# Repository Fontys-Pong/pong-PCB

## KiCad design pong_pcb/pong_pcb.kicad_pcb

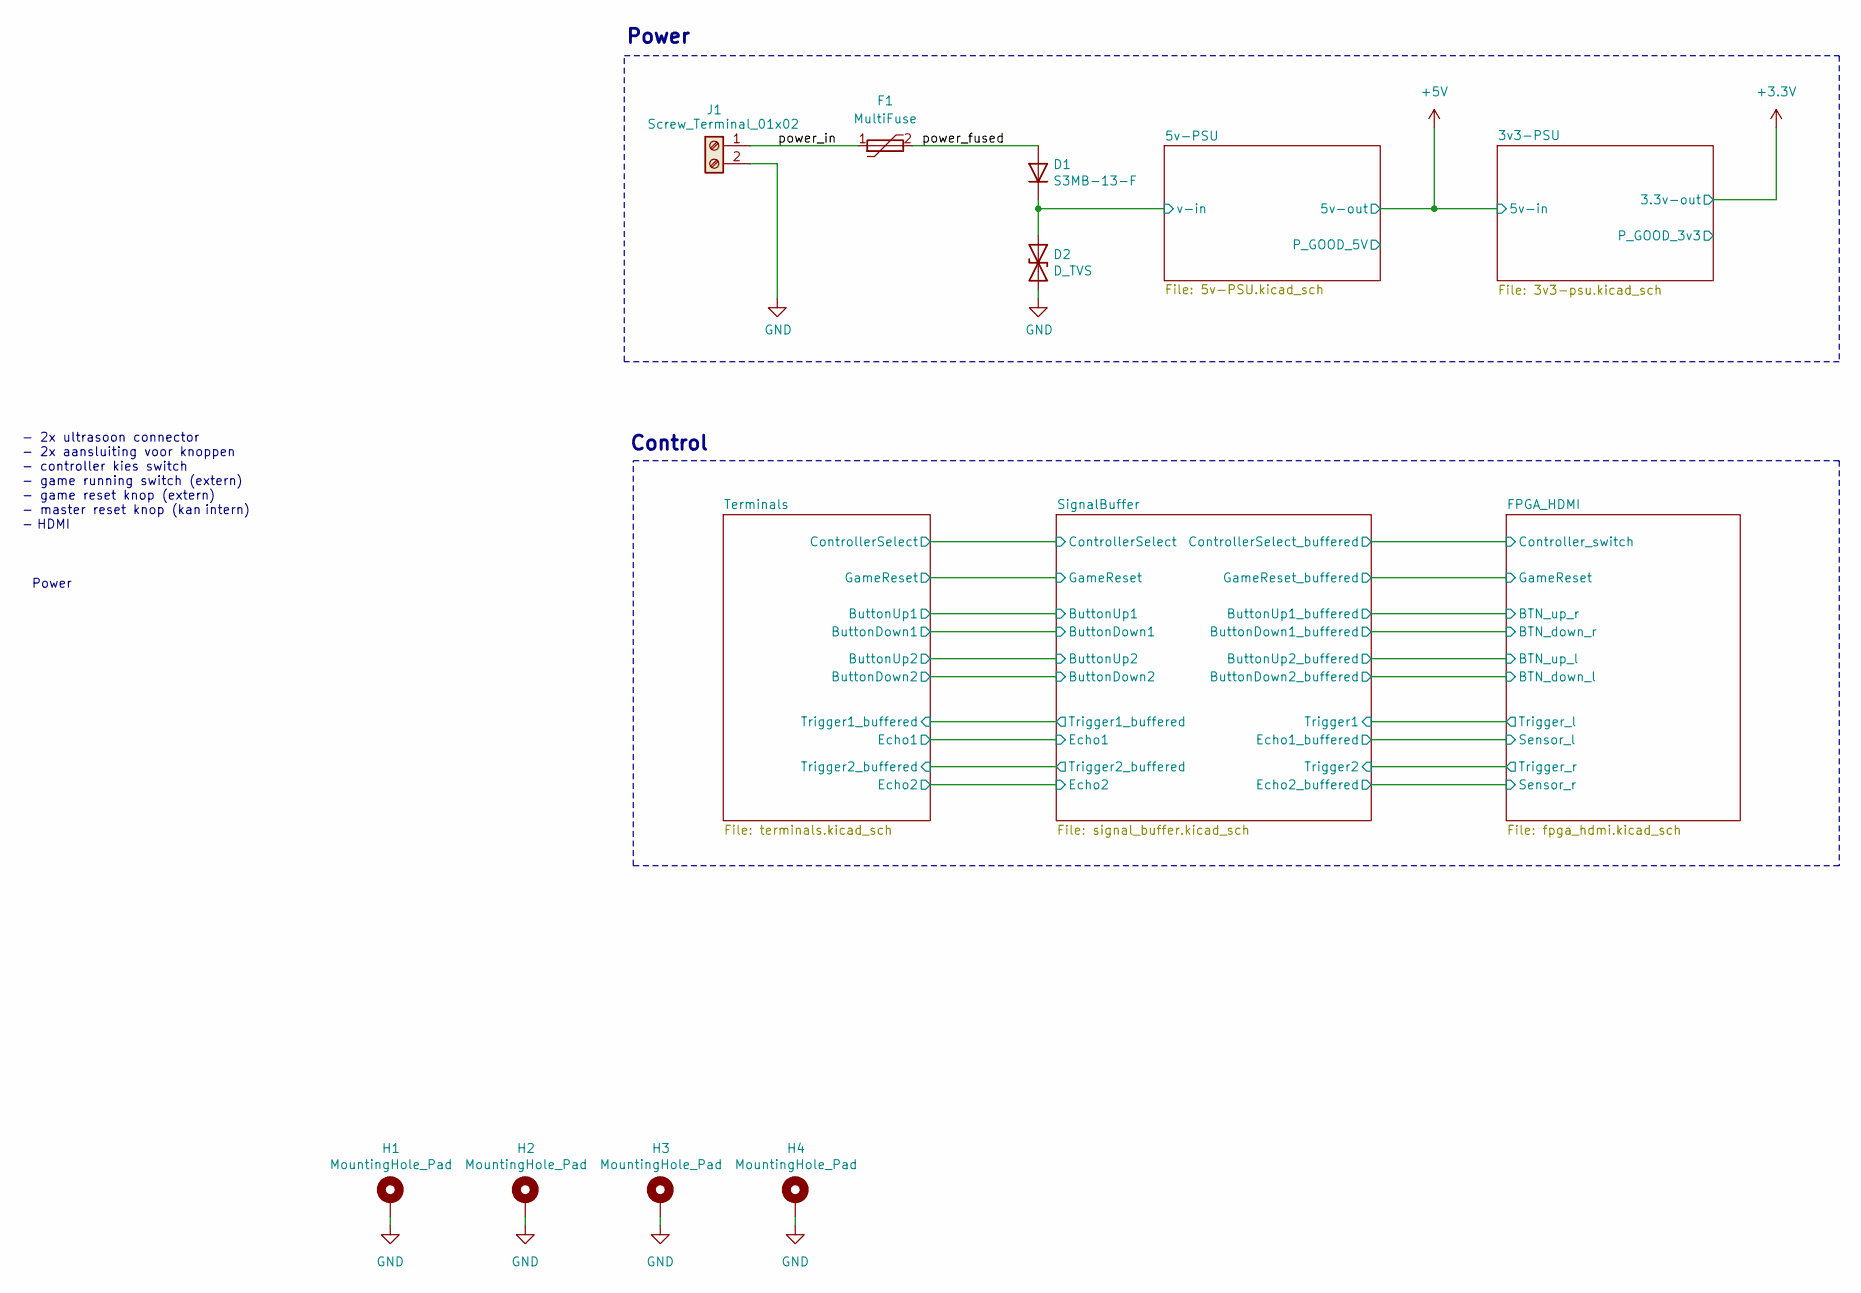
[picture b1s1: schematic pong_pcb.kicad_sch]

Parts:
D1: S3MB-13-F; D_SMB_Handsoldering; Mouser S3MB-13-F
D2: D_TVS; D_SMB_Handsoldering; Mouser 824520281
F1: MultiFuse; Fuse MF-MSMF075 33X-2; Mouser MF-MSMF075/33X-2
H1, H2, H3, H4: MountingHole_Pad; MountingHole_3.2mm_M3_Pad_Via
J1: Screw_Terminal_01x02; PhoenixContact_MSTBA_2,5_2-G-5,08_1x02_P5.08mm_Horizontal

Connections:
/5v-PSU/v-in: D1.1 (K), D2.1 (A1); also elsewhere on the board
/power_fused: D1.2 (A), F1.2
/power_in: F1.1, J1.1
GND: D2.2 (A2), H1.1, H2.1, H3.1, H4.1, J1.2; also elsewhere on the board

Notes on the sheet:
Power
- 2x ultrasoon connector - 2x aansluiting voor knoppen - controller kies switch - game running switch (extern) - game reset knop (extern) - master reset knop (kan intern) - HDMI
Control

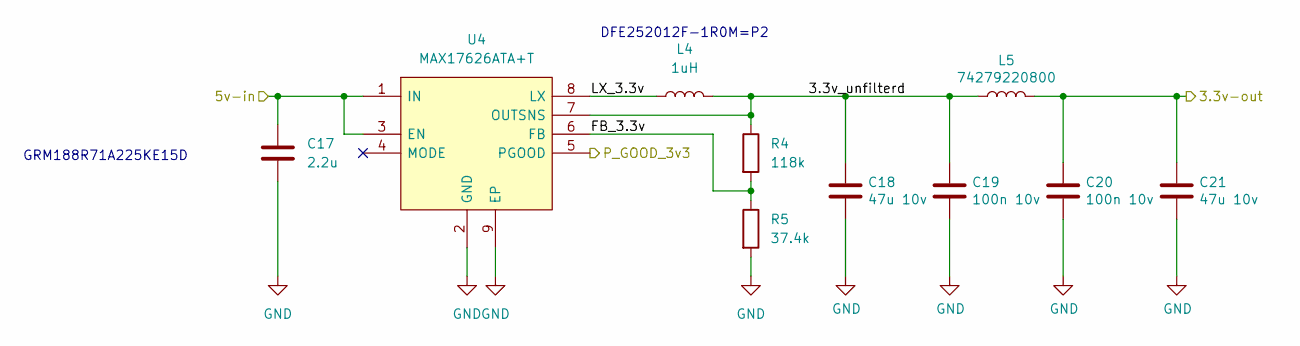
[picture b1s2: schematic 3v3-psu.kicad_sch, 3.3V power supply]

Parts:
C17: 2.2u; C_0603_1608Metric
C18, C21: 47u 10v; C_1206_3216Metric_Pad1.33x1.80mm_HandSolder; Mouser LMK316BC6476ML-T
C19, C20: 100n 10v; C_0603_1608Metric; Mouser LMF105B7103MVHF
L4: 1uH; L_1008_2520Metric
L5: 74279220800; L_0805_2012Metric_Pad1.15x1.40mm_HandSolder; Mouser 74279220800
R4: 118k; R_0603_1608Metric
R5: 37.4k; R_0603_1608Metric
U4: MAX17626ATA+T; SON50P200X200X80-9N-D; Manufacturer_Part_Number MAX17626ATA+T; Mouser Part Number 700-MAX17626ATA+T

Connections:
+3.3V: C20.1, C21.1, L5.2; also elsewhere on the board
+5V: C17.1, U4.1 (IN), U4.3 (EN); also elsewhere on the board
/3v3-PSU/3.3v_unfilterd: C18.1, C19.1, L4.2, L5.1, R4.1, U4.7 (OUTSNS)
/3v3-PSU/FB_3.3v: R4.2, R5.1, U4.6 (FB)
/3v3-PSU/LX_3.3v: L4.1, U4.8 (LX)
/3v3-PSU/P_GOOD_3v3: U4.5 (PGOOD)
GND: C17.2, C18.2, C19.2, C20.2, C21.2, R5.2, U4.2 (GND), U4.9 (EP); also elsewhere on the board

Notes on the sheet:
GRM188R71A225KE15D
DFE252012F-1R0M=P2

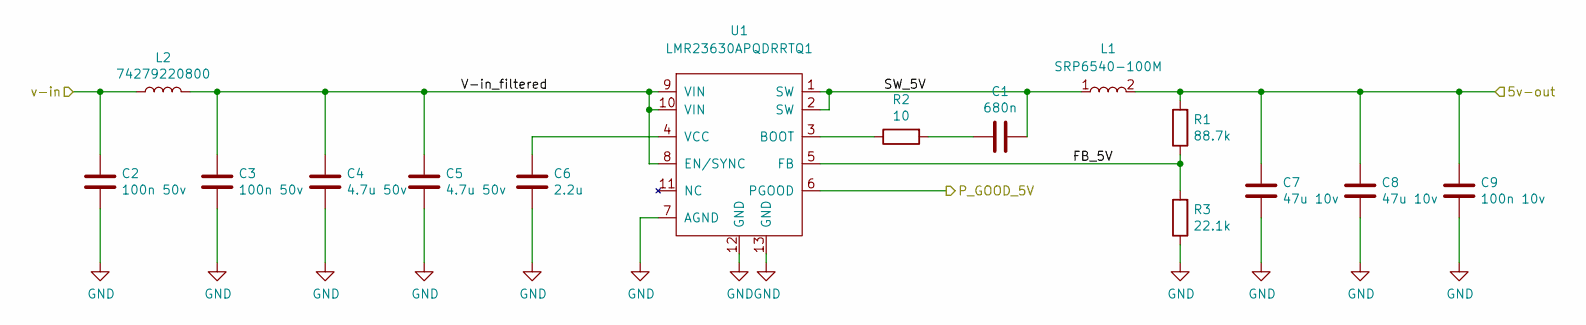
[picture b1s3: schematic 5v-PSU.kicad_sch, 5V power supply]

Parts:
C1: 680n; C_0603_1608Metric_Pad1.08x0.95mm_HandSolder; Mouser CGA3E1X7R1E684K080AC
C2, C3: 100n 50v; C_0805_2012Metric_Pad1.18x1.45mm_HandSolder; Mouser C0805C104KMRECAUTO
C4, C5: 4.7u 50v; C_0805_2012Metric_Pad1.18x1.45mm_HandSolder; Mouser C2012X7R1H475K125AC
C6: 2.2u; C_0603_1608Metric_Pad1.08x0.95mm_HandSolder; Mouser 963-TMK105CBJ225KV-F
C7, C8: 47u 10v; C_1206_3216Metric_Pad1.33x1.80mm_HandSolder; Mouser LMK316BC6476ML-T
C9: 100n 10v; C_0603_1608Metric; Mouser LMF105B7103MVHF
L1: SRP6540-100M; Mouser SRP6540-100M
L2: 74279220800; L_0805_2012Metric_Pad1.15x1.40mm_HandSolder; Mouser 74279220800
R1: 88.7k; R_0603_1608Metric; Mouser ERJ-2RKF8872X
R2: 10; R_0603_1608Metric; Mouser CRCW040210R0FKEDC
R3: 22.1k; R_0603_1608Metric; Mouser ERJ-2RHD2212X
U1: LMR23630APQDRRTQ1; Mouser LMR23630APQDRRTQ1

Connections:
+5V: C7.1, C8.1, C9.1, L1.2, R1.2; also elsewhere on the board
/5v-PSU/FB_5V: R1.1, R3.2, U1.5 (FB)
/5v-PSU/P_GOOD_5V: U1.6 (PGOOD)
/5v-PSU/SW_5V: C1.1, L1.1, U1.1 (SW), U1.2 (SW)
/5v-PSU/V-in_filtered: C3.1, C4.1, C5.1, L2.2, U1.8 (EN/SYNC), U1.9 (VIN), U1.10 (VIN)
/5v-PSU/v-in: C2.1, L2.1; also elsewhere on the board
GND: C2.2, C3.2, C4.2, C5.2, C6.2, C7.2, C8.2, C9.2, R3.1, U1.7 (AGND), U1.12 (GND), U1.13 (GND); also elsewhere on the board
unnamed: C1.2, R2.2
unnamed: R2.1, U1.3 (BOOT)
unnamed: C6.1, U1.4 (VCC)

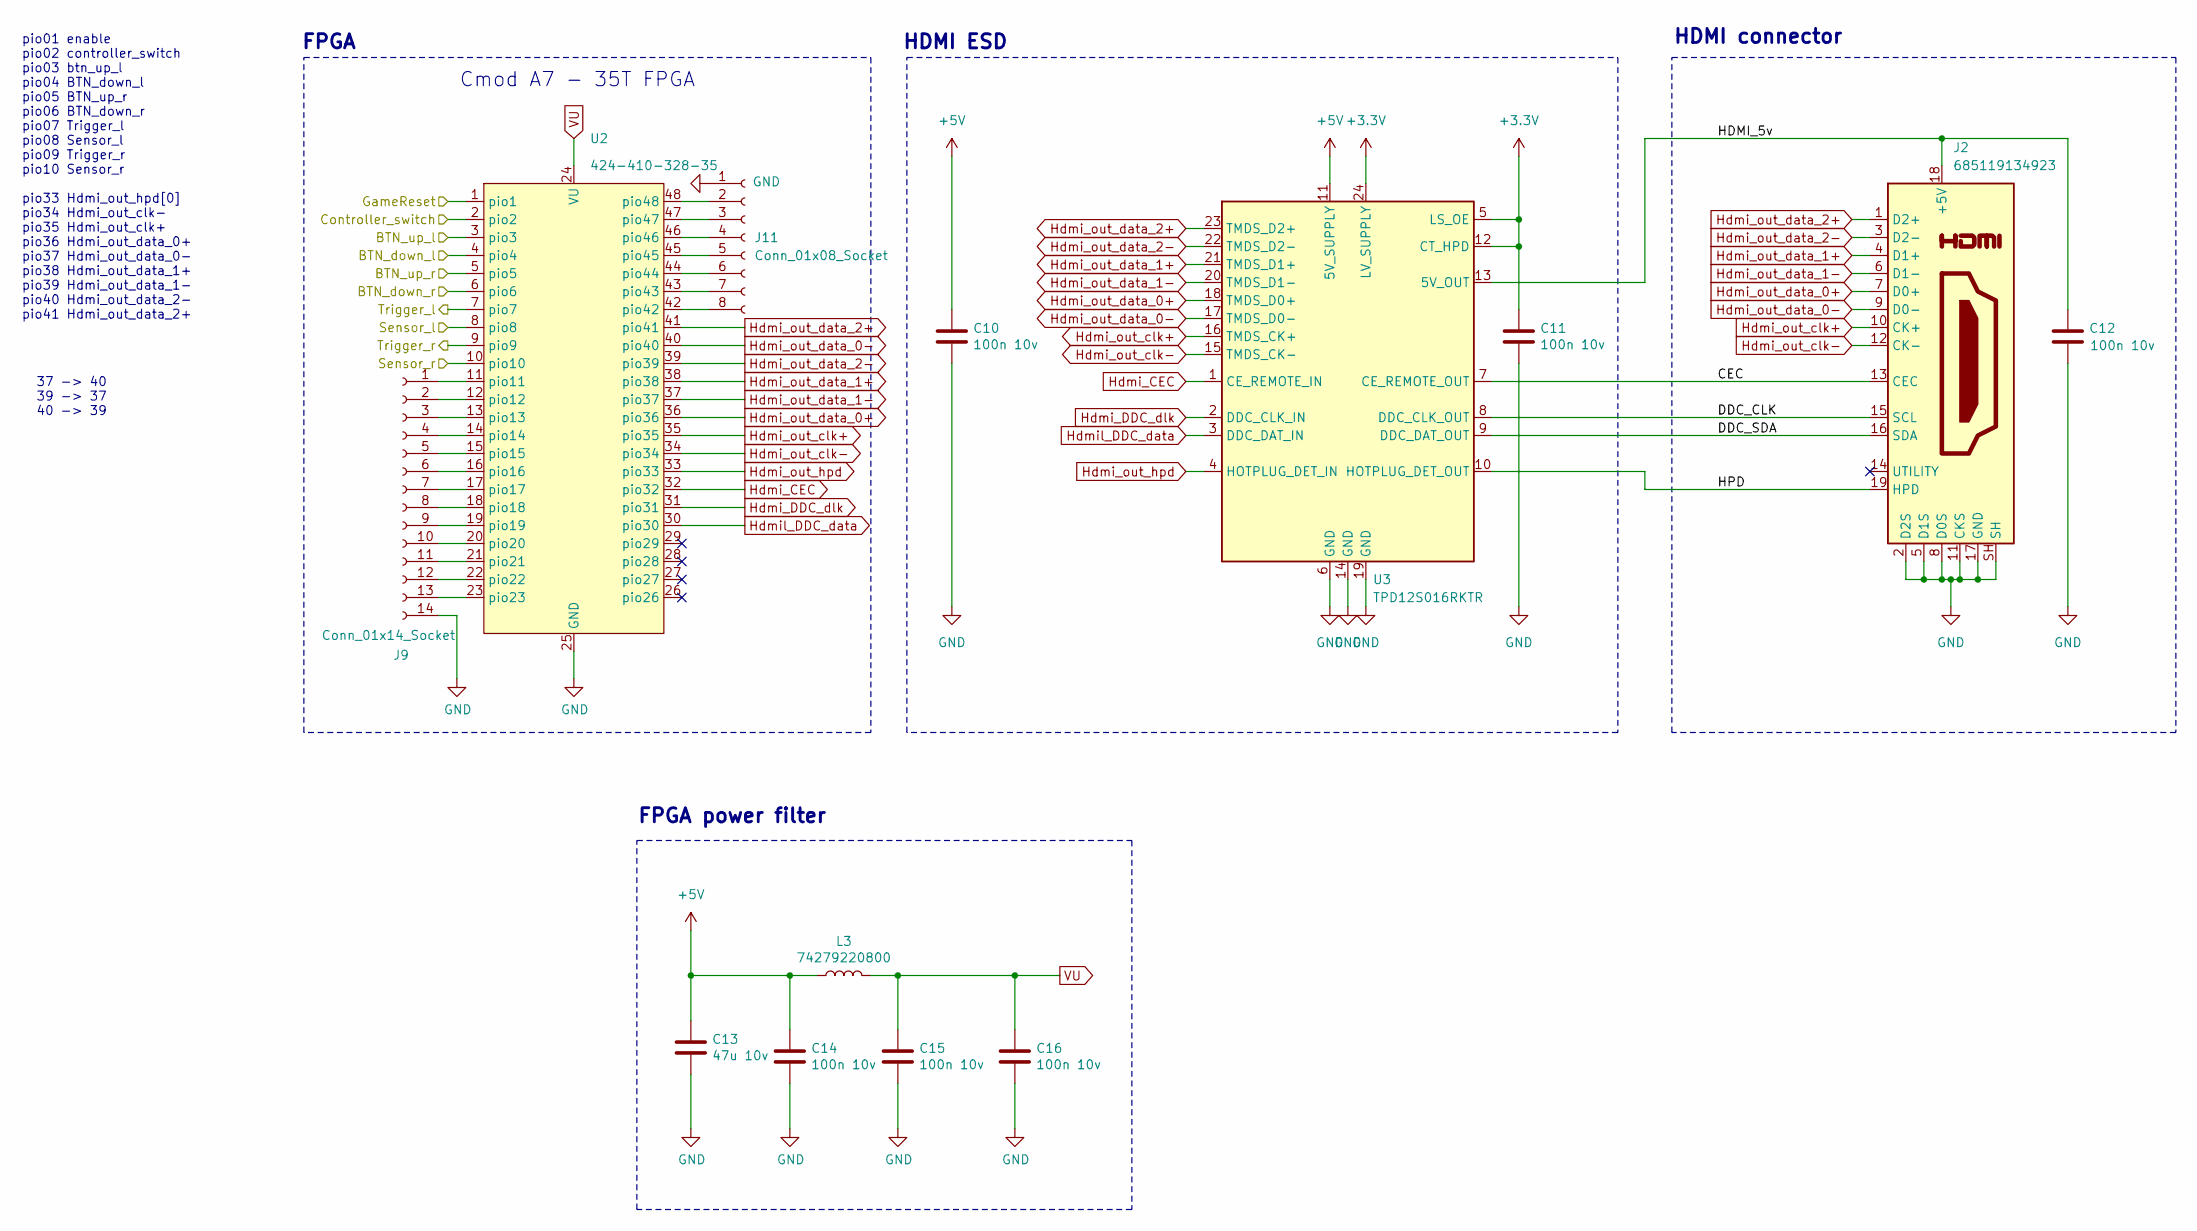
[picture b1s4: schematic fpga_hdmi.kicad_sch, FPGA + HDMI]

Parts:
C10, C11, C12, C14, C15, C16: 100n 10v; C_0603_1608Metric; Mouser LMF105B7103MVHF
C13: 47u 10v; C_1206_3216Metric_Pad1.33x1.80mm_HandSolder; Mouser LMK316BC6476ML-T
J2: 685119134923
J9: Conn_01x14_Socket; PinSocket_2x07_P2.54mm_Vertical
J11: Conn_01x08_Socket; PinSocket_2x04_P2.54mm_Vertical
L3: 74279220800; L_0805_2012Metric_Pad1.15x1.40mm_HandSolder; Mouser 74279220800
U2: CmodA7; Mouser 424-410-328-35
U3: TPD12S016RKTR; TSSOP-24_4.4x7.8mm_P0.65mm

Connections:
+3.3V: C11.1, U3.5 (LS_OE), U3.12 (CT_HPD), U3.24 (LV_SUPPLY); also elsewhere on the board
+5V: C10.1, C13.1, C14.1, L3.1, U3.11 (5V_SUPPLY); also elsewhere on the board
/FPGA_HDMI/BTN_down_l: U2.4 (pio4); also elsewhere on the board
/FPGA_HDMI/BTN_down_r: U2.6 (pio6); also elsewhere on the board
/FPGA_HDMI/BTN_up_l: U2.3 (pio3); also elsewhere on the board
/FPGA_HDMI/BTN_up_r: U2.5 (pio5); also elsewhere on the board
/FPGA_HDMI/CEC: J2.13 (CEC), U3.7 (CE_REMOTE_OUT)
/FPGA_HDMI/Controller_switch: U2.2 (pio2); also elsewhere on the board
/FPGA_HDMI/DDC_CLK: J2.15 (SCL), U3.8 (DDC_CLK_OUT)
/FPGA_HDMI/DDC_SDA: J2.16 (SDA), U3.9 (DDC_DAT_OUT)
/FPGA_HDMI/GameReset: U2.1 (pio1); also elsewhere on the board
/FPGA_HDMI/HDMI_5v: C12.1, J2.18 (+5V), U3.13 (5V_OUT)
/FPGA_HDMI/HPD: J2.19 (HPD), U3.10 (HOTPLUG_DET_OUT)
/FPGA_HDMI/Sensor_l: U2.8 (pio8); also elsewhere on the board
/FPGA_HDMI/Sensor_r: U2.10 (pio10); also elsewhere on the board
/FPGA_HDMI/Trigger_l: U2.7 (pio7); also elsewhere on the board
/FPGA_HDMI/Trigger_r: U2.9 (pio9); also elsewhere on the board
GND: C10.2, C11.2, C12.2, C13.2, C14.2, C15.2, C16.2, J2.2 (D2S), J2.5 (D1S), J2.8 (D0S), J2.11 (CKS), J2.17 (GND), J2.SH, J9.14, J11.1, U2.25 (GND), U3.6 (GND), U3.14 (GND), U3.19 (GND); also elsewhere on the board
Hdmi_CEC: U2.32 (pio32), U3.1 (CE_REMOTE_IN)
Hdmi_DDC_dlk: U2.31 (pio31), U3.2 (DDC_CLK_IN)
Hdmi_out_clk+: J2.10 (CK+), U2.35 (pio35), U3.16 (TMDS_CK+)
Hdmi_out_clk-: J2.12 (CK-), U2.34 (pio34), U3.15 (TMDS_CK-)
Hdmi_out_data_0+: J2.7 (D0+), U2.36 (pio36), U3.18 (TMDS_D0+)
Hdmi_out_data_0-: J2.9 (D0-), U2.40 (pio40), U3.17 (TMDS_D0-)
Hdmi_out_data_1+: J2.4 (D1+), U2.38 (pio38), U3.21 (TMDS_D1+)
Hdmi_out_data_1-: J2.6 (D1-), U2.37 (pio37), U3.20 (TMDS_D1-)
Hdmi_out_data_2+: J2.1 (D2+), U2.41 (pio41), U3.23 (TMDS_D2+)
Hdmi_out_data_2-: J2.3 (D2-), U2.39 (pio39), U3.22 (TMDS_D2-)
Hdmi_out_hpd: U2.33 (pio33), U3.4 (HOTPLUG_DET_IN)
Hdmil_DDC_data: U2.30 (pio30), U3.3 (DDC_DAT_IN)
unnamed: J9.1, U2.11 (pio11)
unnamed: J9.2, U2.12 (pio12)
unnamed: J9.3, U2.13 (pio13)
unnamed: J9.4, U2.14 (pio14)
unnamed: J9.5, U2.15 (pio15)
unnamed: J9.6, U2.16 (pio16)
unnamed: J9.7, U2.17 (pio17)
unnamed: J9.8, U2.18 (pio18)
unnamed: J9.9, U2.19 (pio19)
unnamed: J9.10, U2.20 (pio20)
unnamed: J9.11, U2.21 (pio21)
unnamed: J9.12, U2.22 (pio22)
unnamed: J9.13, U2.23 (pio23)
unnamed: J11.2, U2.48 (pio48)
unnamed: J11.3, U2.47 (pio47)
unnamed: J11.4, U2.46 (pio46)
unnamed: J11.5, U2.45 (pio45)
unnamed: J11.6, U2.44 (pio44)
unnamed: J11.7, U2.43 (pio43)
unnamed: J11.8, U2.42 (pio42)
VU: C15.1, C16.1, L3.2, U2.24 (VU)

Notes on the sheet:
FPGA
pio01 enable pio02 controller_switch pio03 btn_up_l pio04 BTN_down_l pio05 BTN_up_r pio06 BTN_down_r pio07 Trigger_l pio08 Sensor_l pio09 Trigger_r pio10 Sensor_r pio33 Hdmi_out_hpd[0] pio34 Hdmi_out_clk- pio35 Hdmi_out_clk+ pio36 Hdmi_out_data_0+ pio37 Hdmi_out_data_0- pio38 Hdmi_out_data_1+ pio39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
FPGA power filter
Cmod A7 - 35T FPGA
37 -> 40 39 -> 37 40 -> 39
HDMI ESD
HDMI connector

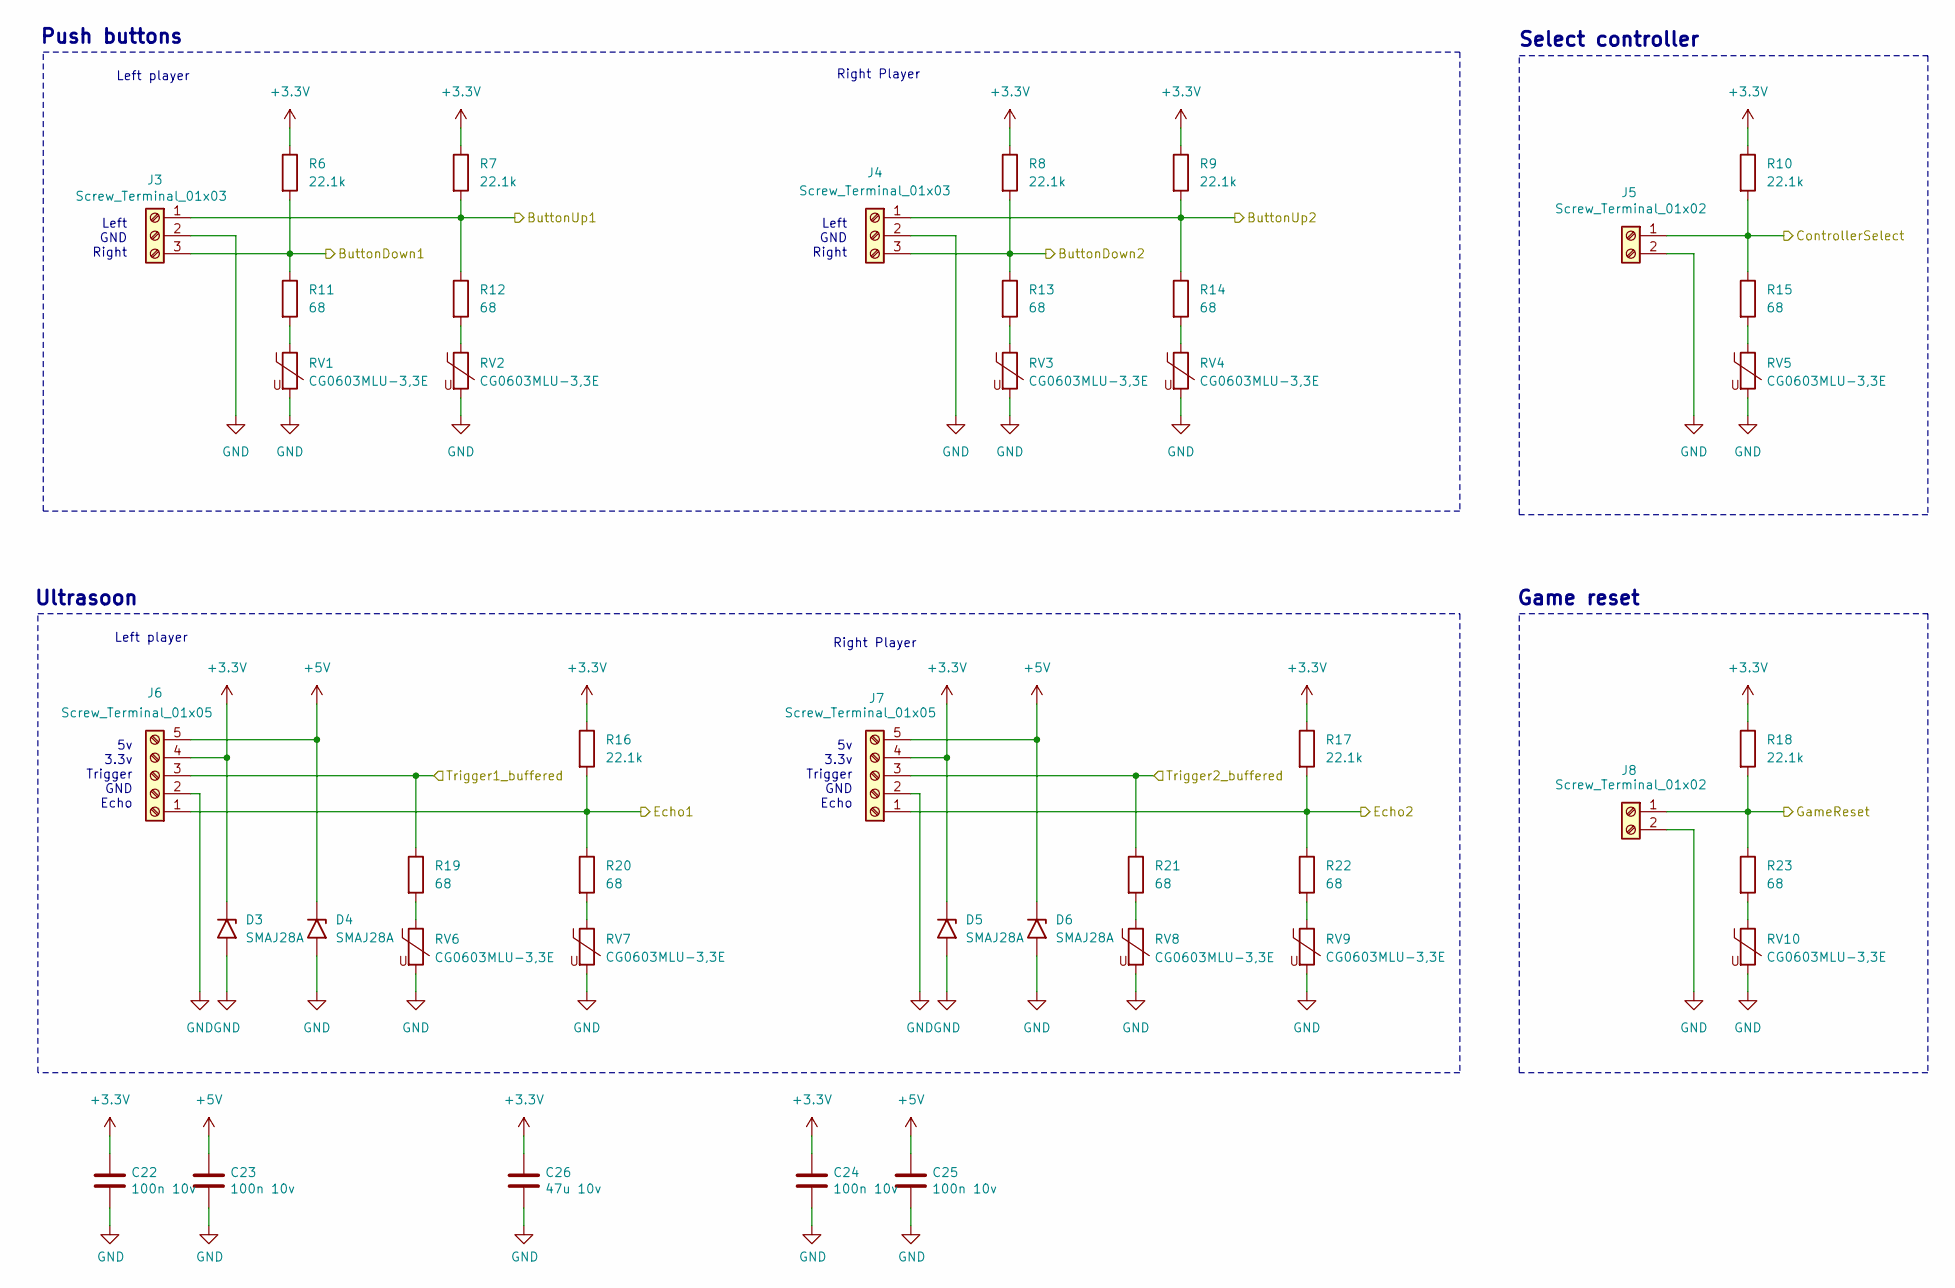
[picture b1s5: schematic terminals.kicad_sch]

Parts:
C22, C23, C24, C25: 100n 10v; C_0603_1608Metric; Mouser LMF105B7103MVHF
C26: 47u 10v; C_1206_3216Metric_Pad1.33x1.80mm_HandSolder; Mouser LMK316BC6476ML-T
D3, D4, D5, D6: SMAJ28A; D_SMA
J3, J4: Screw_Terminal_01x03; PhoenixContact_MSTBA_2,5_3-G-5,08_1x03_P5.08mm_Horizontal
J5, J8: Screw_Terminal_01x02; PhoenixContact_MSTBA_2,5_2-G-5,08_1x02_P5.08mm_Horizontal
J6, J7: Screw_Terminal_01x05; PhoenixContact_MSTBA_2,5_5-G-5,08_1x05_P5.08mm_Horizontal
R6, R7, R8, R9, R10, R16, R17, R18: 22.1k; R_0603_1608Metric
R11, R12, R13, R14, R15, R19, R20, R21, R22, R23: 68; R_0603_1608Metric
RV1, RV2, RV3, RV4, RV5, RV6, RV7, RV8, RV9, RV10: CG0603MLU-3,3E; R_0603_1608Metric

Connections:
+3.3V: C22.1, C24.1, C26.1, D3.1 (A1), D5.1 (A1), J6.4, J7.4, R6.1, R7.1, R8.1, R9.1, R10.1, R16.1, R17.1, R18.1; also elsewhere on the board
+5V: C23.1, C25.1, D4.1 (A1), D6.1 (A1), J6.5, J7.5; also elsewhere on the board
/SignalBuffer/ButtonDown1: J3.3, R6.2, R11.1; also elsewhere on the board
/SignalBuffer/ButtonDown2: J4.3, R8.2, R13.1; also elsewhere on the board
/SignalBuffer/ButtonUp1: J3.1, R7.2, R12.1; also elsewhere on the board
/SignalBuffer/ButtonUp2: J4.1, R9.2, R14.1; also elsewhere on the board
/SignalBuffer/ControllerSelect: J5.1, R10.2, R15.1; also elsewhere on the board
/SignalBuffer/Echo1: J6.1, R16.2, R20.1; also elsewhere on the board
/SignalBuffer/Echo2: J7.1, R17.2, R22.1; also elsewhere on the board
/SignalBuffer/GameReset: J8.1, R18.2, R23.1; also elsewhere on the board
/SignalBuffer/Trigger1_buffered: J6.3, R19.1; also elsewhere on the board
/SignalBuffer/Trigger2_buffered: J7.3, R21.1; also elsewhere on the board
GND: C22.2, C23.2, C24.2, C25.2, C26.2, D3.2 (A2), D4.2 (A2), D5.2 (A2), D6.2 (A2), J3.2, J4.2, J5.2, J6.2, J7.2, J8.2, RV1.2, RV2.2, RV3.2, RV4.2, RV5.2, RV6.2, RV7.2, RV8.2, RV9.2, RV10.2; also elsewhere on the board
unnamed: R11.2, RV1.1
unnamed: R12.2, RV2.1
unnamed: R13.2, RV3.1
unnamed: R14.2, RV4.1
unnamed: R15.2, RV5.1
unnamed: R19.2, RV6.1
unnamed: R20.2, RV7.1
unnamed: R21.2, RV8.1
unnamed: R22.2, RV9.1
unnamed: R23.2, RV10.1

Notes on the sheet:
5v 3.3v Trigger GND Echo
Ultrasoon
Game reset
Left GND Right
Push buttons
Left player
Right Player
Select controller

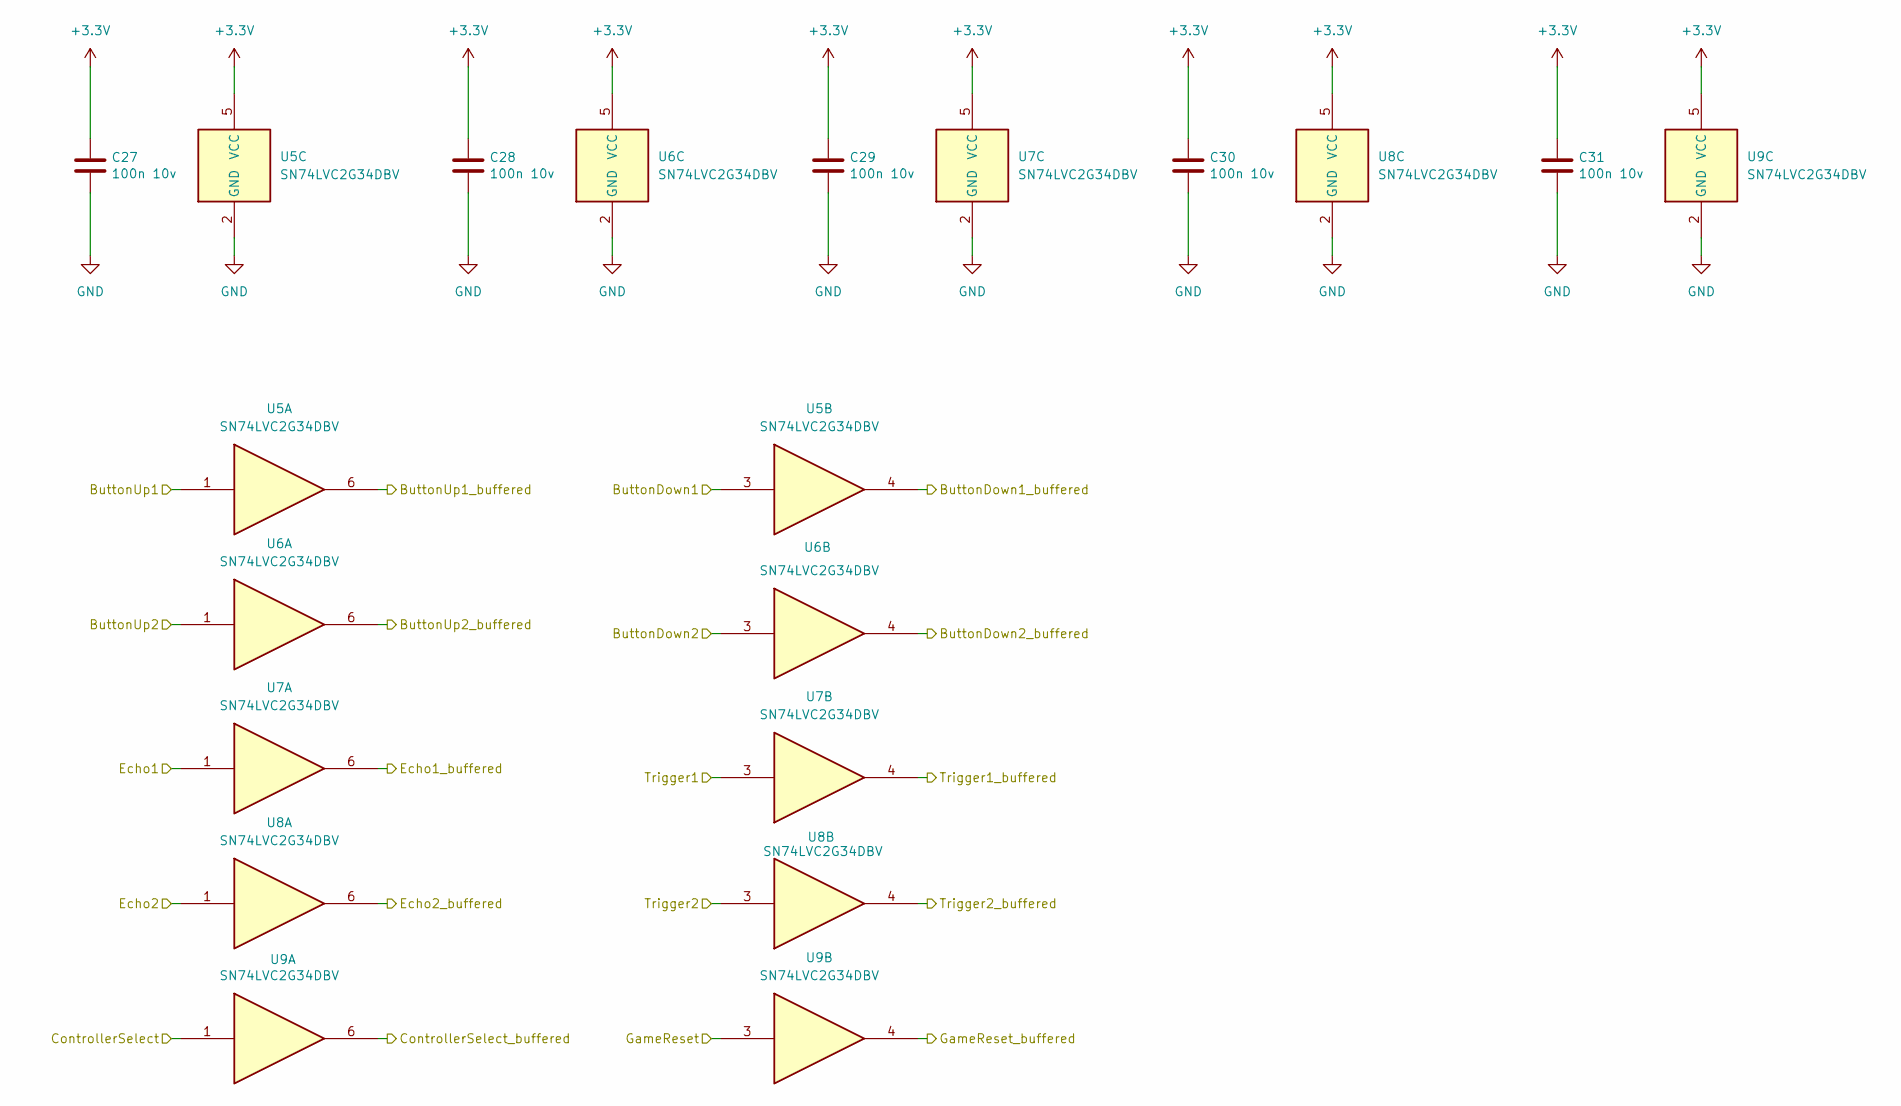
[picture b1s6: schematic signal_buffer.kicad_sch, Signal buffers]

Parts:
C27, C28, C29, C30, C31: 100n 10v; C_0603_1608Metric; Mouser LMF105B7103MVHF
U5, U6, U7, U8, U9: SN74LVC2G34DBV; SOT-23-6_Handsoldering

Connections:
+3.3V: C27.1, C28.1, C29.1, C30.1, C31.1, U5.5 (VCC), U6.5 (VCC), U7.5 (VCC), U8.5 (VCC), U9.5 (VCC); also elsewhere on the board
/FPGA_HDMI/BTN_down_l: U6.4; also elsewhere on the board
/FPGA_HDMI/BTN_down_r: U5.4; also elsewhere on the board
/FPGA_HDMI/BTN_up_l: U6.6; also elsewhere on the board
/FPGA_HDMI/BTN_up_r: U5.6; also elsewhere on the board
/FPGA_HDMI/Controller_switch: U9.6; also elsewhere on the board
/FPGA_HDMI/GameReset: U9.4; also elsewhere on the board
/FPGA_HDMI/Sensor_l: U7.6; also elsewhere on the board
/FPGA_HDMI/Sensor_r: U8.6; also elsewhere on the board
/FPGA_HDMI/Trigger_l: U7.3; also elsewhere on the board
/FPGA_HDMI/Trigger_r: U8.3; also elsewhere on the board
/SignalBuffer/ButtonDown1: U5.3; also elsewhere on the board
/SignalBuffer/ButtonDown2: U6.3; also elsewhere on the board
/SignalBuffer/ButtonUp1: U5.1; also elsewhere on the board
/SignalBuffer/ButtonUp2: U6.1; also elsewhere on the board
/SignalBuffer/ControllerSelect: U9.1; also elsewhere on the board
/SignalBuffer/Echo1: U7.1; also elsewhere on the board
/SignalBuffer/Echo2: U8.1; also elsewhere on the board
/SignalBuffer/GameReset: U9.3; also elsewhere on the board
/SignalBuffer/Trigger1_buffered: U7.4; also elsewhere on the board
/SignalBuffer/Trigger2_buffered: U8.4; also elsewhere on the board
GND: C27.2, C28.2, C29.2, C30.2, C31.2, U5.2 (GND), U6.2 (GND), U7.2 (GND), U8.2 (GND), U9.2 (GND); also elsewhere on the board

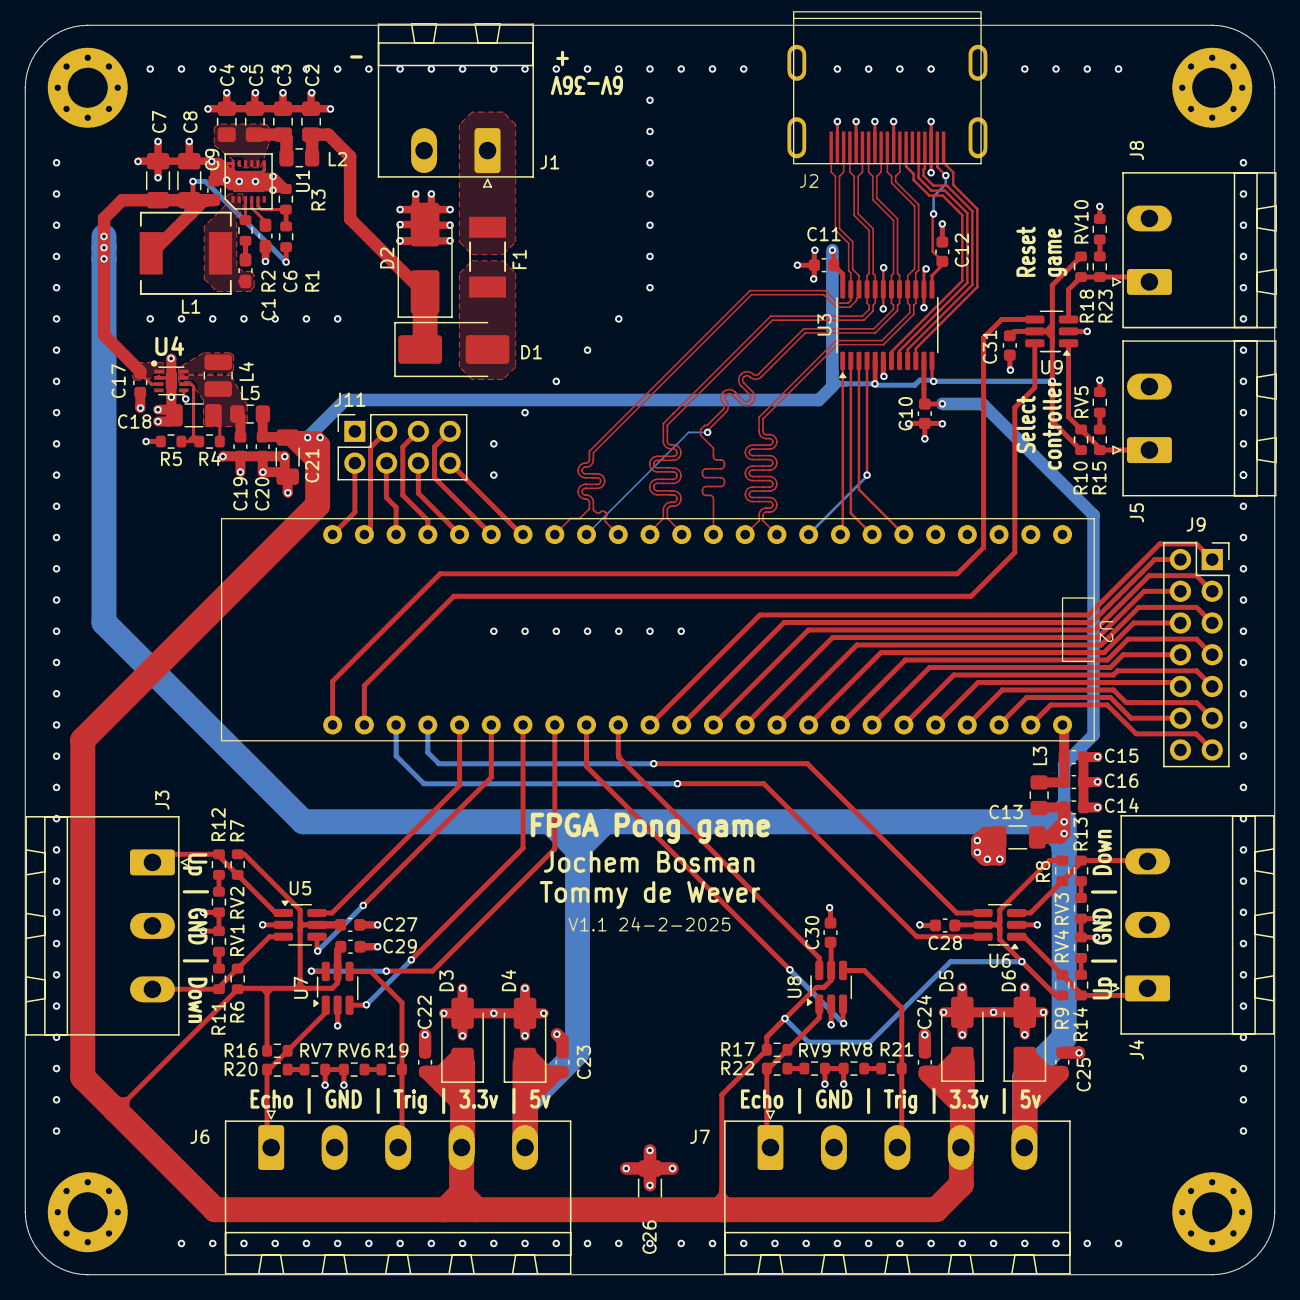
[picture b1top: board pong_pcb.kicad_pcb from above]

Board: 4 copper layers, 100.0 x 100.0 mm, 99 parts (0 on the bottom side), 83 nets.

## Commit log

2024-04-03 Schema
2024-04-03 Update schema and add packages
2024-04-05 Add HDMI layout
    And others
2024-04-05 PCB indeling maken
2024-04-07 Update schema and route PCB
2024-04-08 Other connectors
2024-06-18 Add header pins
2024-06-19 Update TODOs
2024-09-25 Gerbers
2025-02-22 Interactive BOM + PDF Schema
2025-02-24 Fix HDMI pinout
